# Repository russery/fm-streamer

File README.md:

# FM Streamer
Are there not a lot of good FM radio stations in your vicinity? Have you ever wished you could receive your hometown station on your FM radio while you're away? Well this is the project for you!

This is a simple ESP32/ESP8266 project that grabs an MP3 internet stream and bridges it to an FM transmitter, so that you can listen to the stream on your old-school FM radio.

# Setup
If you're on Linux or Mac (or any system with GNU Make installed), install [arduino-cli](https://github.com/arduino/arduino-cli). This project is set up to work out of the box with it, and this will save you having to set up the ESP32/ESP8266 and required libraries in your Arduino IDE.

1. Run `make config-tools` to install libraries and ESP32/ESP8266 core.
1. Rename `arduino_secrets.h.example` to `arduino_secrets.h` and change the wifi SSID and password in it to match the network you wish to attach to.
1. If you want to change the radio streams, edit them in the `StationList` struct in fm-streamer.ino.
1. Power on your board, connect its serial port to your computer, and see how the serial port comes up on your computer (e.g., `/dev/cu.usbserial-xxxx` or `COM1`, etc.). You'll use this value in the next step
1. Run `make program SERIAL_PORT=<serialport> MCU_TYPE=<esp32|esp8266>` (replacing \<serialport\> with the name of the serial port from the previous step, and using either "esp32" or "esp8266" as the MCU_TYPE) to compile the code and upload it to your board.

# Usage
Once you've followed the above steps and your board is programmed, the FM Streamer should connect to your wifi network, begin streaming the first mp3 stream in `StationList` (defined in webserver.h), and automatically broadcast over FM. There is a status output on the serial console that will tell you what's going on with the board as well.

I've implemented a web interface to the FM Streamer that allows you to control the station, volume, and transmit power of the FM Streamer. Note that this doesn't work on the ESP8266, as it runs out of RAM between the web server and audio streaming. However, it works well on the ESP32. Here's what it looks like:

---

# Under the Hood
This project consists of three hardware components:
1. [ESP32 dev board](https://www.amazon.com/dp/B08D5ZD528) or [ESP3266 NodeMCU v1.0](https://www.amazon.com/gp/product/B010O1G1ES/)
1. [Adafruit UDA1334A I2S Stereo DAC breakout board](https://www.adafruit.com/product/3678)
1. [Adafruit Si4713 FM Transmitter breakout board](https://www.adafruit.com/product/1958)

## Hardware
These are wired together like so (for the ESP32):

Everything is powered from the ESP32 board's 3.3V output. The Si4713 FM transmitter is connected to the ESP32 over I2C, the UDA1334 DAC is connected to it over I2S, and then the UDA1334 DAC outputs audio to the Si4713 transmitter via analog stereo audio.

I also wired a 4.7kΩ resistor from each of the DAC's analog audio outputs to GND to provide a bit of loading for it. I found that this helped reduce noise and clipping on the FM transmitter's input, although I did not experiment much with values or whether this is truly necessary.

## Software
The software makes use of the [ESP8266Audio](https://github.com/earlephilhower/ESP8266Audio) library and [Adafruit's Si4713](https://github.com/adafruit/Adafruit-Si4713-Library) driver. The webserver uses the [ESPAsynWebserver](https://github.com/me-no-dev/ESPAsyncWebServer/) library.

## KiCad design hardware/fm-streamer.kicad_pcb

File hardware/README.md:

# REV0 Hardware

## Hardware Errata
- USB connector backwards
- Silkscreen overlap on some components
- R21 puts chip in SPI mode... should be DNP'd

I2S format:
16-bit
Normal clock (rising edge)

TODO:
- fix hardware errata
- update top level readme with board images and latest hardware config

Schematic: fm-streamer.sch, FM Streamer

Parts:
C1, C13, C15, C18: 0.1u; C_0402_1005Metric; MPN GCM155R71C104KA55J
C2, C3, C12, C14, C16, C19, C20, C21, C22, C23: 10u; C_0603_1608Metric; MPN GRT188C81A106ME13D
C4, C5, C6, C7, C8, C9, C10, C11, C17: 22n; C_0402_1005Metric; MPN GCM155R71E223KA55J
J1: USB_A; USB_A_Plug_Molex_0480371000_90_deg_mount
L1: 120n; L_0603_1608Metric; MPN LQW18ANR12G00D
R1, R2, R14, R28, R29, R30: 0; R_0402_1005Metric
R3, R12: 4.7k; R_0402_1005Metric
R4, R5, R6, R7, R8, R9, R10, R11, R17, R22, R23, R26, R27: 100; R_0402_1005Metric
R13: 1; R_0402_1005Metric
R15, R16, R18, R19, R20, R21: 10k; R_0402_1005Metric
R24, R25: 220k; R_0402_1005Metric
TP1: TestPoint; TestPoint_THTPad_D2.0mm_Drill1.0mm
U1: ESP32_DevKit_V1_DOIT; esp32_devkit_v1_doit; MPN B08D5ZD528
U2: PCM1772PWR; MPN PCM1772PWR
U3: SI4721; QFN-20-3X3MM; MPN SI4721-B20-GM

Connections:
+3V3: C3.2, C14.1, C15.1, C17.1, C18.1, C21.1, R3.2, R12.2, R13.2, U1.16, U2.12, U3.10 (VIO), U3.11 (VDD)
+5V: C1.1, C2.1, J1.1, U1.15; also elsewhere on the board
/ANTENNA: R14.2
/DAC_CLK_R: R8.2, U1.4
/I2S_DATA_R: R5.2, U1.24
/I2S_DCLK_R: R6.2, U1.21
/I2S_WCLK_R: R4.2, U1.22
/RAD_CLK_R: R7.2, U1.8
/SPI_CLK_R: R10.2, U1.6
/SPI_CS_R: R11.2, U1.5
/SPI_MOSI_R: R9.2, U1.7
AUDIO_L: C23.1, R22.1, R27.1
AUDIO_R: C22.2, R23.1, R26.1
DAC_REFCLK: C8.1, R8.1, U2.16
DAC_~RST~: R15.1, U1.26, U2.4
GND: C1.2, C2.2, C3.1, C4.2, C5.2, C6.2, C7.2, C8.2, C9.2, C10.2, C11.2, C12.2, C13.2, C14.2, C15.2, C16.2, C17.2, C18.2, C21.2, C22.1, C23.2, J1.4, J1.5, L1.2, R1.1, R2.1, R15.2, R16.2, R17.2, R18.2, R19.2, R20.2, R21.2, R24.2, R25.1, U1.14, U1.17, U2.5, U2.6, U3.2 (FMI), U3.3 (RFGND), U3.12 (GND), U3.21 (GND); also elsewhere on the board
I2C_SCL: R12.1, U1.10, U3.7 (SCLK)
I2C_SDA: R3.1, U1.9, U3.8 (SDIO)
I2S_DATA: C5.1, R5.1, R29.2, U3.13 (ROUT/DIN)
I2S_DCLK: C6.1, R6.1, R28.2, U3.17 (GPO3/DCLK)
I2S_WCLK: C4.1, R4.1, R30.2, U3.14 (LOUT/DFS)
unnamed: C12.1, C13.1, R13.1, U2.11
unnamed: C16.1, U2.7
unnamed: C19.1, R24.1, R26.2
unnamed: C19.2, U2.8
unnamed: C20.1, R25.2, R27.2
unnamed: C20.2, U2.9
unnamed 27: J1.2, R2.2; also elsewhere on the board
unnamed 28: J1.3, R1.2; also elsewhere on the board
unnamed: L1.1, R14.1, TP1.1, U3.4 (TXO)
unnamed: R17.1, U2.10
unnamed: R19.1, U3.6 (~SEN)
unnamed: R20.1, U3.19 (GPO1)
unnamed: R21.1, U3.18 (GPO2/~INT)
unnamed: R22.2, U3.16 (LIN/DFS)
unnamed: R23.2, U3.15 (RIN/DOUT)
unnamed: R28.1, U2.3
unnamed: R29.1, U2.2
unnamed: R30.1, U2.1
RADIO_REFCLK: C7.1, R7.1, U3.9 (RCLK)
RADIO_~RST~: R18.1, U1.13, U3.5 (~RST)
SPI_CLK: C10.1, R10.1, U2.14
SPI_MOSI: C9.1, R9.1, U2.13
SPI_~CS~: C11.1, R11.1, R16.1, U2.15

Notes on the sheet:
I2S DAC DNP’d - only included to hedge against issues with FM Transmitter I2S interface.
SEN=GND -> I2C ADDR=0x11
Testpoint for optional wire antenna
http://esp32.net/images/DOIT/ESP32-DevKit-V1/DOIT_ESP32-DevKit_Schematic.pdf

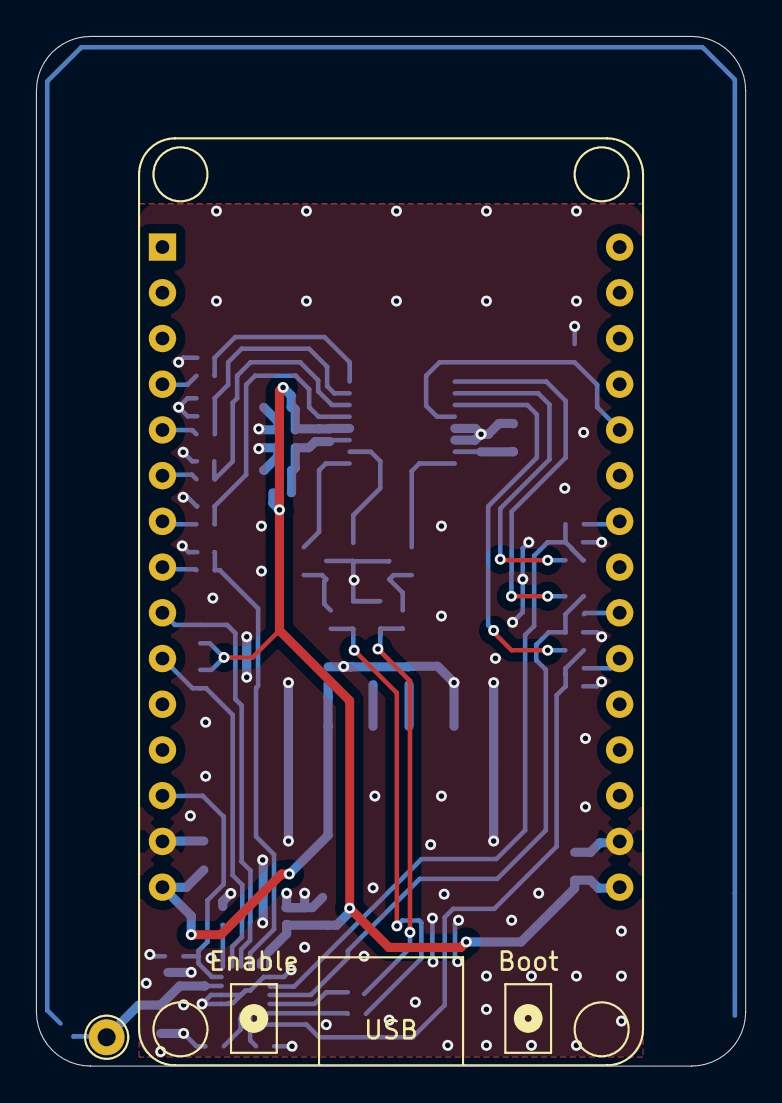
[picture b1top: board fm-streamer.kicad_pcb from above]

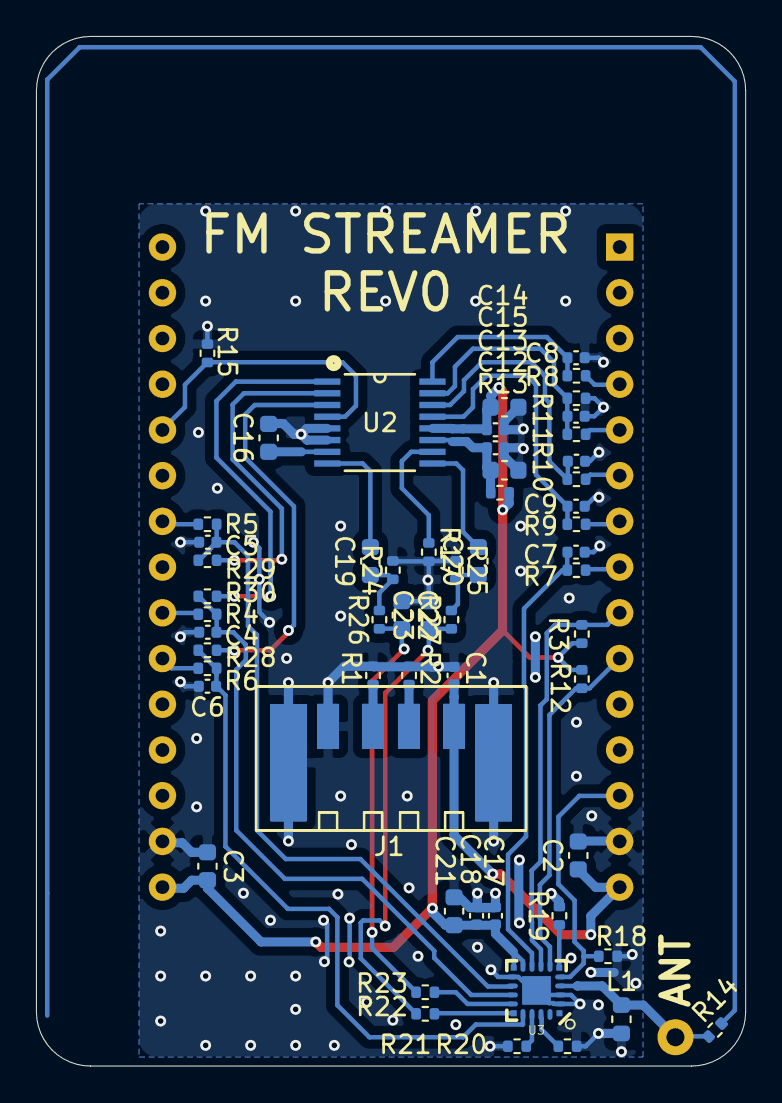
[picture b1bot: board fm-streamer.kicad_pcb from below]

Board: 2 copper layers, 39.4 x 57.2 mm, 61 parts (59 on the bottom side), 43 nets.

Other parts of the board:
J1#2, J1#3: USB_A; USB_A_Plug_Molex_0480371000_90_deg_mount

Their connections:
+5V: J1#2.1, J1#3.1; also elsewhere on the board
GND: J1#2.4, J1#2.5, J1#3.4, J1#3.5; also elsewhere on the board
unnamed 27: J1#2.2, J1#3.2; also elsewhere on the board
unnamed 28: J1#2.3, J1#3.3; also elsewhere on the board

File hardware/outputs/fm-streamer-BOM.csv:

Reference, Quantity, Value, Footprint, Datasheet, MFG, MPN
C1 C13 C15 C18 ,4,"0.1u","Capacitor_SMD:C_0402_1005Metric","~","Murata","GCM155R71C104KA55J"
C4 C5 C6 C7 C8 C9 C10 C11 C17 ,9,"22n","Capacitor_SMD:C_0402_1005Metric","~","Murata","GCM155R71E223KA55J"
C2 C3 C12 C14 C16 C19 C20 C21 C22 C23 ,10,"10u","Capacitor_SMD:C_0603_1608Metric","~","Murata","GRT188C81A106ME13D"
J1 ,1,"USB_A","Connector_USB:USB_A_Plug_Molex_0480371000_90_deg_mount"," ~","Molex","0480371000"
L1 ,1,"120n","Inductor_SMD:L_0603_1608Metric","~","Murata","LQW18ANR12G00D"
R13 ,1,"1","Resistor_SMD:R_0402_1005Metric","~","Panasonic","ERJ-2BQJ1R0X"
R1 R2 R14 R28 R29 R30 ,6,"0","Resistor_SMD:R_0402_1005Metric","~","Stackpole","RMCF0402ZT0R00"
R15 R16 R18 R19 R20 R21 ,6,"10k","Resistor_SMD:R_0402_1005Metric","~","Panasonic","ERJ-2RKF1002X"
R24 R25 ,2,"220k","Resistor_SMD:R_0402_1005Metric","~","Panasonic","ERJ-2RKF2203X"
R4 R5 R6 R7 R8 R9 R10 R11 R17 R22 R23 R26 R27 ,13,"100","Resistor_SMD:R_0402_1005Metric","~","Panasonic","ERJ-2RKF1000X"
R3 R12 ,2,"4.7k","Resistor_SMD:R_0402_1005Metric","~","Panasonic","ERJ-2RKF4701X"
TP1 ,1,"TestPoint","TestPoint:TestPoint_THTPad_D2.0mm_Drill1.0mm","~","~","~"
U1 ,1,"ESP32_DevKit_V1_DOIT","esp32_devkit_v1_doit:esp32_devkit_v1_doit","https://www.amazon.com/gp/product/B08D5ZD528/","Amazon","B08D5ZD528"
U2 ,1,"PCM1772PWR","footprints:PCM1772PWR","","Texas Instruments","PCM1772PWR"
U3 ,1,"SI4721","SI4721:QFN-20-3X3MM","","Silicon Labs","SI4721-B20-GM"

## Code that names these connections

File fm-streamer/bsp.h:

/*
Includes pin definitions and other hardware-specific things.

Copyright (C) 2021  Robert Ussery

This program is free software: you can redistribute it and/or modify
it under the terms of the GNU General Public License as published by
the Free Software Foundation, either version 3 of the License, or
(at your option) any later version.

This program is distributed in the hope that it will be useful,
but WITHOUT ANY WARRANTY; without even the implied warranty of
MERCHANTABILITY or FITNESS FOR A PARTICULAR PURPOSE.  See the
GNU General Public License for more details.

You should have received a copy of the GNU General Public License
along with this program.  If not, see <https://www.gnu.org/licenses/>.
*/

#ifndef __BSP_H
#define __BSP_H

#include <Arduino.h>

#define HARDWARE_REV0

class BSP {
public:
#if defined(ESP32)
  // Status LED and states:
  static constexpr char LED_STREAMING_PIN PROGMEM = 2;
  static constexpr char LED_OFF PROGMEM = LOW;
  static constexpr char LED_ON PROGMEM = HIGH;

#elif defined(ESP8266)
  // Status LED and states:
  static constexpr char LED_STREAMING_PIN PROGMEM = 16;
  static constexpr char LED_OFF PROGMEM = HIGH;
  static constexpr char LED_ON PROGMEM = LOW;
#endif // ESP32 / ESP8266

#if defined(HARDWARE_PROTO_ESP8266)
  static constexpr uint RADIO_RESET_PIN PROGMEM = 12;
  static constexpr uint SI47XX_CHIP_VERSION = 13; // SI4713
  static constexpr uint SI47xx_I2C_ADDR PROGMEM = 0x63;

  static constexpr uint I2S_BCLK_PIN PROGMEM = 15;
  static constexpr uint I2S_WCLK_PIN PROGMEM = 2;
  static constexpr uint I2S_DATA_PIN PROGMEM = 3;

  static constexpr uint I2C_SDA_PIN PROGMEM = 4;
  static constexpr uint I2C_SCL_PIN PROGMEM = 5;

#elif defined(HARDWARE_PROTO_ESP32)
  static constexpr uint RADIO_RESET_PIN PROGMEM = 23;
  static constexpr uint SI47XX_CHIP_VERSION = 13; // SI4713
  static constexpr uint SI47xx_I2C_ADDR PROGMEM = 0x63;

  static constexpr uint I2S_BCLK_PIN PROGMEM = 4;
  static constexpr uint I2S_WCLK_PIN PROGMEM = 17;
  static constexpr uint I2S_DATA_PIN PROGMEM = 16;

  static constexpr uint I2C_SDA_PIN PROGMEM = 21;
  static constexpr uint I2C_SCL_PIN PROGMEM = 22;

#elif defined(HARDWARE_REV0)
  static constexpr uint RADIO_RESET_PIN PROGMEM = 13;
  static constexpr uint RADIO_CLK_PIN PROGMEM = 25;
  static constexpr uint SI47XX_CHIP_VERSION = 21; // SI4721
  static constexpr uint SI47xx_I2C_ADDR PROGMEM = 0x11;

  static constexpr uint I2S_BCLK_PIN PROGMEM = 16;
  static constexpr uint I2S_WCLK_PIN PROGMEM = 17;
  static constexpr uint I2S_DATA_PIN PROGMEM = 18;

  static constexpr uint I2C_SDA_PIN PROGMEM = 26;
  static constexpr uint I2C_SCL_PIN PROGMEM = 27;

  // static constexpr uint DAC_RESET_PIN PROGMEM = 21;
  // static constexpr uint DAC_CLK_PIN PROGMEM = 34;

  // static constexpr uint SPI_SCK_PIN PROGMEM = 32;
  // static constexpr uint SPI_MOSI_PIN PROGMEM = 33;
  // static constexpr uint DAC_SPI_CS PROGMEM = 35;

#endif // Hardware versions

  static void StartSi47xxClock(uint freq_hz);
  static void InitLED(void);
  static void SetLED(bool state);
  static void Loop(void);

private:
  static constexpr uint32_t LED_MAX_BRIGHTNESS PROGMEM = 100;
  static constexpr uint32_t LED_MIN_BRIGHTNESS PROGMEM = 5;
  static bool LED_on_;
};

#endif // __BSP_H

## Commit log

2021-04-08 arduino-cli bash script and files roughed out
2021-04-14 Changed to use makefile instead of shell script
2021-04-14 Removed arduino-cli config file and made config-tools target to auto-gen
2021-04-14 basic streaming and I2S output working
2021-04-14 Added FM radio tuner code (hacked in)... everything works
2021-04-14 refactored to move streaming to InternetStream class
2021-04-14 added GPLv3 license
2021-04-15 dropped serial console, rearchitecting to use webpage for interaction
2021-04-16 got rid of standalone webpage, added fm_radio, lots of refactoring
2021-04-16 debugging memory issues
2021-04-16 Tweaked buffer size to debug heap corruption issue
2021-04-19 everything working except the streamer: webpage, persistent settings, fm radio config
2021-04-19 hacked out webserver, streamer-only mode
2021-04-19 Added PID-control of audio levels, added #define to remove webserver
2021-04-19 tuned PID loop, added LED indicator for streaming
2021-04-20 adding docs and clang-tidy
2021-04-20 Added clang-format and cppcheck
2021-04-21 fleshed out readme and diagrams
2021-04-21 Added auto-reset and changed library imports to be consistent with implementation
2021-04-21 stubbed out kicad
2021-04-21 fixed compile issues
2021-04-21 minor cleanup and fixes
2021-04-22 Added ESP32 support
2021-04-22 ran cppcheck
2021-04-22 Updated README with ESP32 references
2021-04-25 Everything working on ESP32 hardware
2021-04-25 Added bsp.h, changed to cpps, cleaned up includes and dead code
2021-04-25 refactored to remove webserver and config from main file
2021-04-26 moved config init and mdns start to later in startup
2021-04-26 fixed issue with changing stations
2021-04-27 Added in autovolume config setting
2021-04-27 Updated docs for ESP32
2021-04-27 added webpage screenshot
2021-04-27 moved config out of webserver
2021-04-27 minor cleanup
2021-04-27 prettied up website, added in include guards for .h files
2021-04-27 updated webpage image
2021-04-27 OTA updates working, although not compatible with arduino-cli (yet)
2021-04-27 enabled OTA password
2021-05-01 Migrated to local Si4713 library from Adafruit git library, added I2S support, untested
2021-05-01 Disabled OTA auth for blank password, temporarily disabled I2S stream start/stop
2021-05-01 si4713 basic functionality works
2021-05-01 debugged operation and retuned autovolume PID loop
2021-05-01 added mp3->stop() to stream.flush(), added BBC World Service stream
2021-05-01 Increased stream buffer size
2021-05-02 roughing out schematics
2021-05-02 schematics nominally finished, moving on to PCB
2021-05-02 rough placement and routing complete, needs cleanup
2021-05-03 cleaning up routing
2021-05-03 added 3D body for Molex USB connector, layout cleanup
2021-05-04 ready for fab quote
2021-05-05 Rev0 out to fab
2021-05-05 roughing in bsp support
2021-05-05 fixed some build issues with ESP8266 and got hardware compile switches working
2021-05-05 made BSP a class with static members, added PWM output for radio clock (untested)
2021-05-18 working on support for Rev0 hardware (untested)
2021-05-19 Rev0 tested and working, needs minor cleanup
2021-05-19 cleanup
2021-05-19 Swapped in KEXP for BBC World
2021-05-19 cleanup and made LED glow
2021-05-23 fixed blinkenlight
